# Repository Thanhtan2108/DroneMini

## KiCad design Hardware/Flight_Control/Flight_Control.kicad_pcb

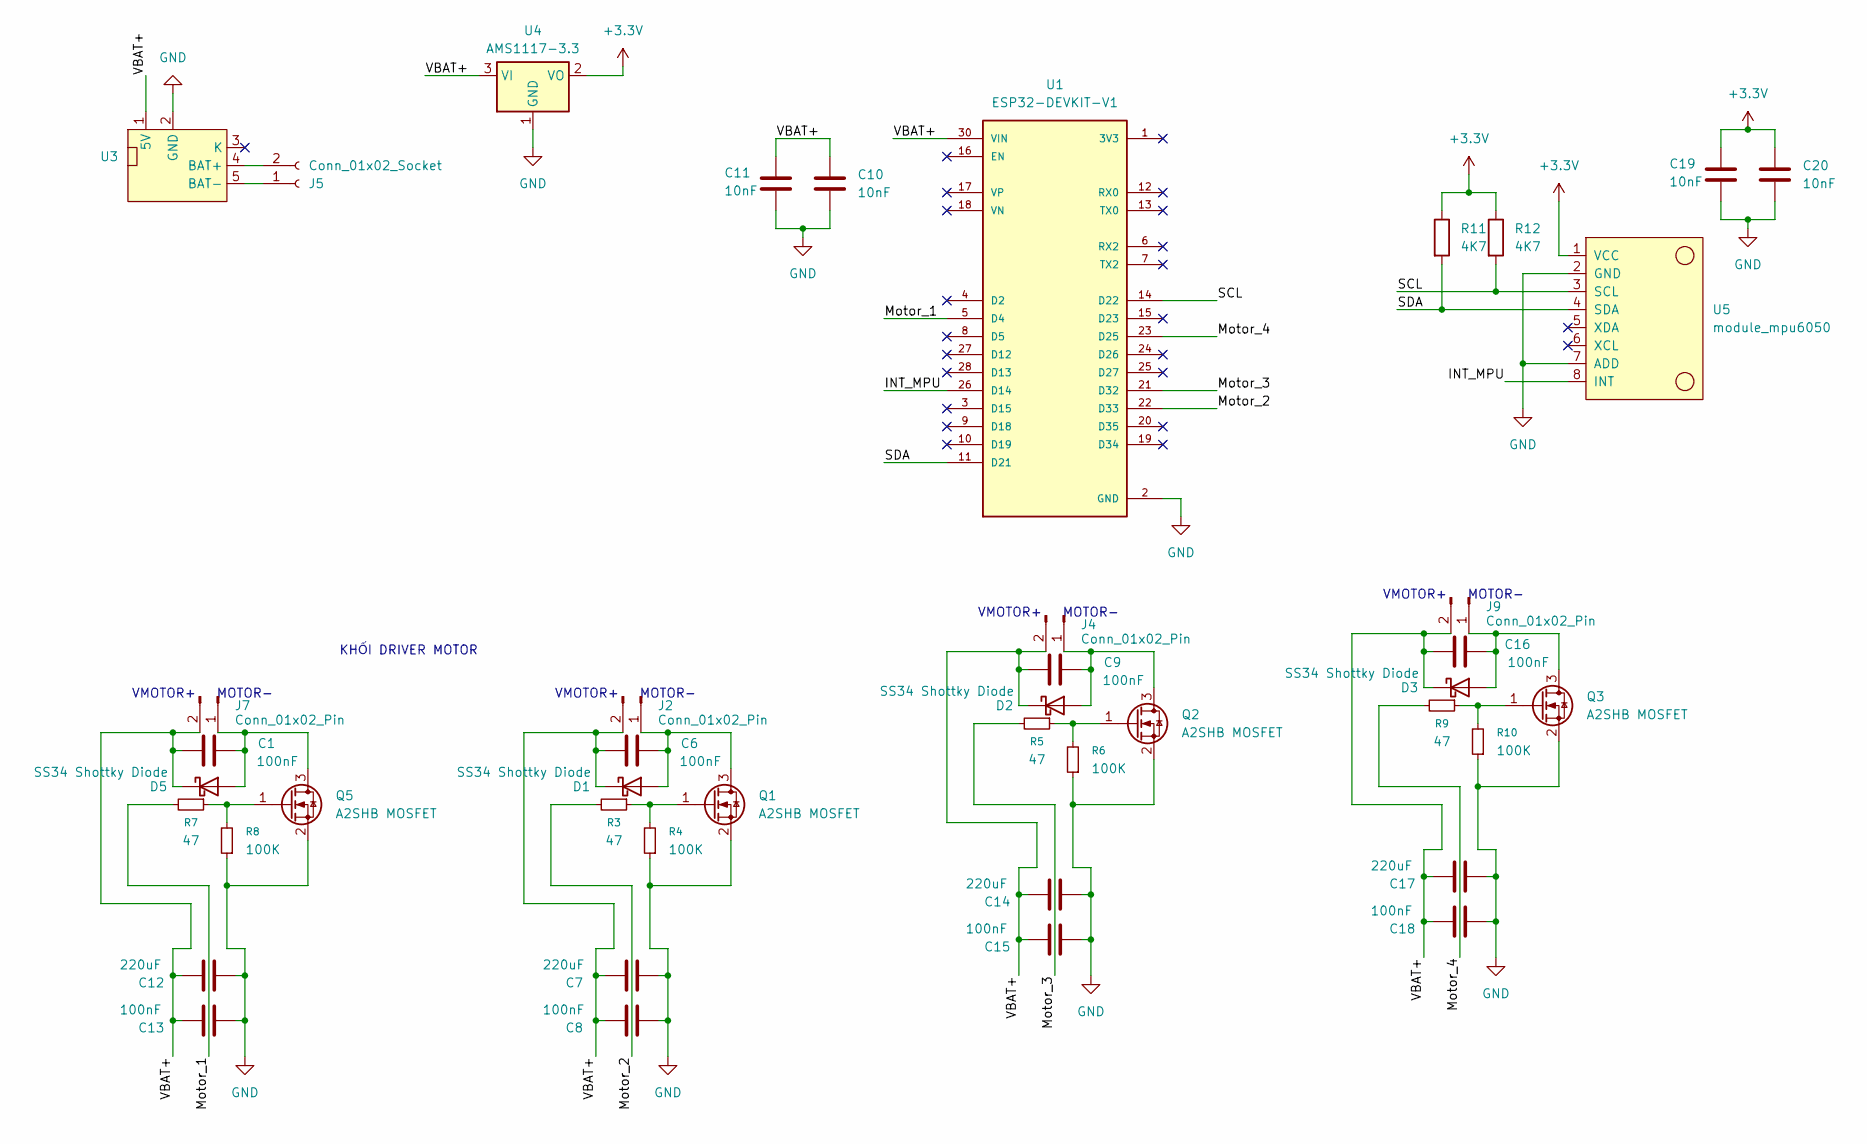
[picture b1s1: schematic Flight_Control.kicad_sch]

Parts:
C1, C6, C8, C9, C13, C15, C16, C18: 100nF; C_0805_2012Metric_Pad1.18x1.45mm_HandSolder
C7, C12, C14, C17: 220uF; C_0805_2012Metric_Pad1.18x1.45mm_HandSolder
C10, C11, C19, C20: 10nF; C_0805_2012Metric_Pad1.18x1.45mm_HandSolder
D1, D2, D3, D5: SS34 Shottky Diode; D_SMA
J2, J4, J7, J9: Conn_01x02_Pin; JST_PH_S2B-PH-K_1x02_P2.00mm_Horizontal
J5: Conn_01x02_Socket; JST_PH_S2B-PH-K_1x02_P2.00mm_Horizontal
Q1, Q2, Q3, Q5: A2SHB MOSFET; SOT-23
R3, R5, R7, R9: 47; R_0805_2012Metric_Pad1.20x1.40mm_HandSolder
R4, R6, R8, R10: 100K; R_0805_2012Metric_Pad1.20x1.40mm_HandSolder
R11, R12: 4K7; R_0805_2012Metric_Pad1.20x1.40mm_HandSolder
U1: ESP32-DEVKIT-V1; MODULE_ESP32_DEVKIT_V1; PARTREV N/A
U3: Type-C_USB_5V_2A_Boost_Converter
U4: AMS1117-3.3; SOT-223-3_TabPin2
U5: module_mpu6050

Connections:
+3.3V: C19.1, C20.1, R11.1, R12.1, U4.2 (VO), U5.1 (VCC)
/INT_MPU: U1.26 (D14), U5.8 (INT)
/Motor_1: R7.2, U1.5 (D4)
/Motor_2: R3.2, U1.22 (D33)
/Motor_3: R5.2, U1.21 (D32)
/Motor_4: R9.2, U1.23 (D25)
/SCL: R12.2, U1.14 (D22), U5.3 (SCL)
/SDA: R11.2, U1.11 (D21), U5.4 (SDA)
/VBAT+: C1.1, C6.1, C7.2, C8.2, C9.1, C10.1, C11.1, C12.2, C13.2, C14.2, C15.2, C16.1, C17.2, C18.2, D1.1 (K), D2.1 (K), D3.1 (K), D5.1 (K), J2.2, J4.2, J7.2, J9.2, U1.30 (VIN), U3.1 (5V), U4.3 (VI)
GND: C7.1, C8.1, C10.2, C11.2, C12.1, C13.1, C14.1, C15.1, C17.1, C18.1, C19.2, C20.2, Q1.2 (S), Q2.2 (S), Q3.2 (S), Q5.2 (S), R4.1, R6.1, R8.1, R10.1, U1.2 (GND), U1.29 (GND), U3.2 (GND), U4.1 (GND), U5.2 (GND), U5.7 (ADD)
unnamed: C6.2, D1.2 (A), J2.1, Q1.3 (D)
unnamed: C9.2, D2.2 (A), J4.1, Q2.3 (D)
unnamed: C16.2, D3.2 (A), J9.1, Q3.3 (D)
unnamed: C1.2, D5.2 (A), J7.1, Q5.3 (D)
unnamed: J5.1, U3.5 (BAT-)
unnamed: J5.2, U3.4 (BAT+)
unnamed: Q1.1 (G), R3.1, R4.2
unnamed: Q2.1 (G), R5.1, R6.2
unnamed: Q3.1 (G), R9.1, R10.2
unnamed: Q5.1 (G), R7.1, R8.2

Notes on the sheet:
MOTOR-
VMOTOR+
KHỐI DRIVER MOTOR

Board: 2 copper layers, 43 parts (0 on the bottom side), 20 nets, no tracks yet.

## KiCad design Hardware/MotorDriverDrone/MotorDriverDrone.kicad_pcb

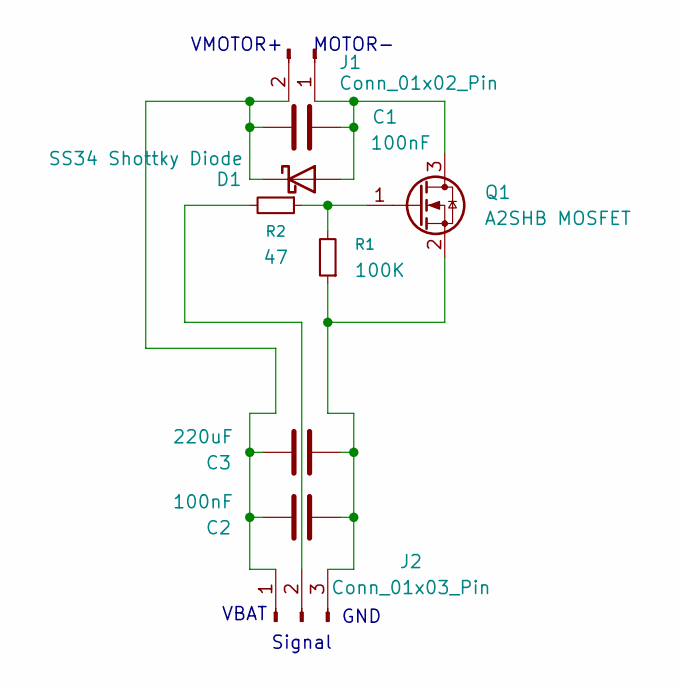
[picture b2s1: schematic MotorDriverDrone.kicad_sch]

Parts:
C1, C2: 100nF; C_0805_2012Metric_Pad1.18x1.45mm_HandSolder
C3: 220uF; C_0805_2012Metric_Pad1.18x1.45mm_HandSolder
D1: SS34 Shottky Diode; D_SMA
J1: Conn_01x02_Pin; JST_PH_S2B-PH-K_1x02_P2.00mm_Horizontal
J2: Conn_01x03_Pin; JST_PH_S3B-PH-K_1x03_P2.00mm_Horizontal
Q1: A2SHB MOSFET; SOT-23
R1: 100K; R_0805_2012Metric_Pad1.20x1.40mm_HandSolder
R2: 47; R_0805_2012Metric_Pad1.20x1.40mm_HandSolder

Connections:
unnamed: C1.2, D1.2 (A), J1.1, Q1.3 (D)
unnamed: C1.1, C2.2, C3.2, D1.1 (K), J1.2, J2.1
unnamed: J2.2, R2.2
unnamed: C2.1, C3.1, J2.3, Q1.2 (S), R1.1
unnamed: Q1.1 (G), R1.2, R2.1

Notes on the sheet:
MOTOR-
GND
VMOTOR+
Signal
VBAT

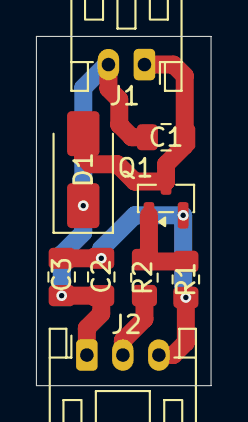
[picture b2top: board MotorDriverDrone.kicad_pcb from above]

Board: 2 copper layers, 9.7 x 19.4 mm, 9 parts (0 on the bottom side), 5 nets.
